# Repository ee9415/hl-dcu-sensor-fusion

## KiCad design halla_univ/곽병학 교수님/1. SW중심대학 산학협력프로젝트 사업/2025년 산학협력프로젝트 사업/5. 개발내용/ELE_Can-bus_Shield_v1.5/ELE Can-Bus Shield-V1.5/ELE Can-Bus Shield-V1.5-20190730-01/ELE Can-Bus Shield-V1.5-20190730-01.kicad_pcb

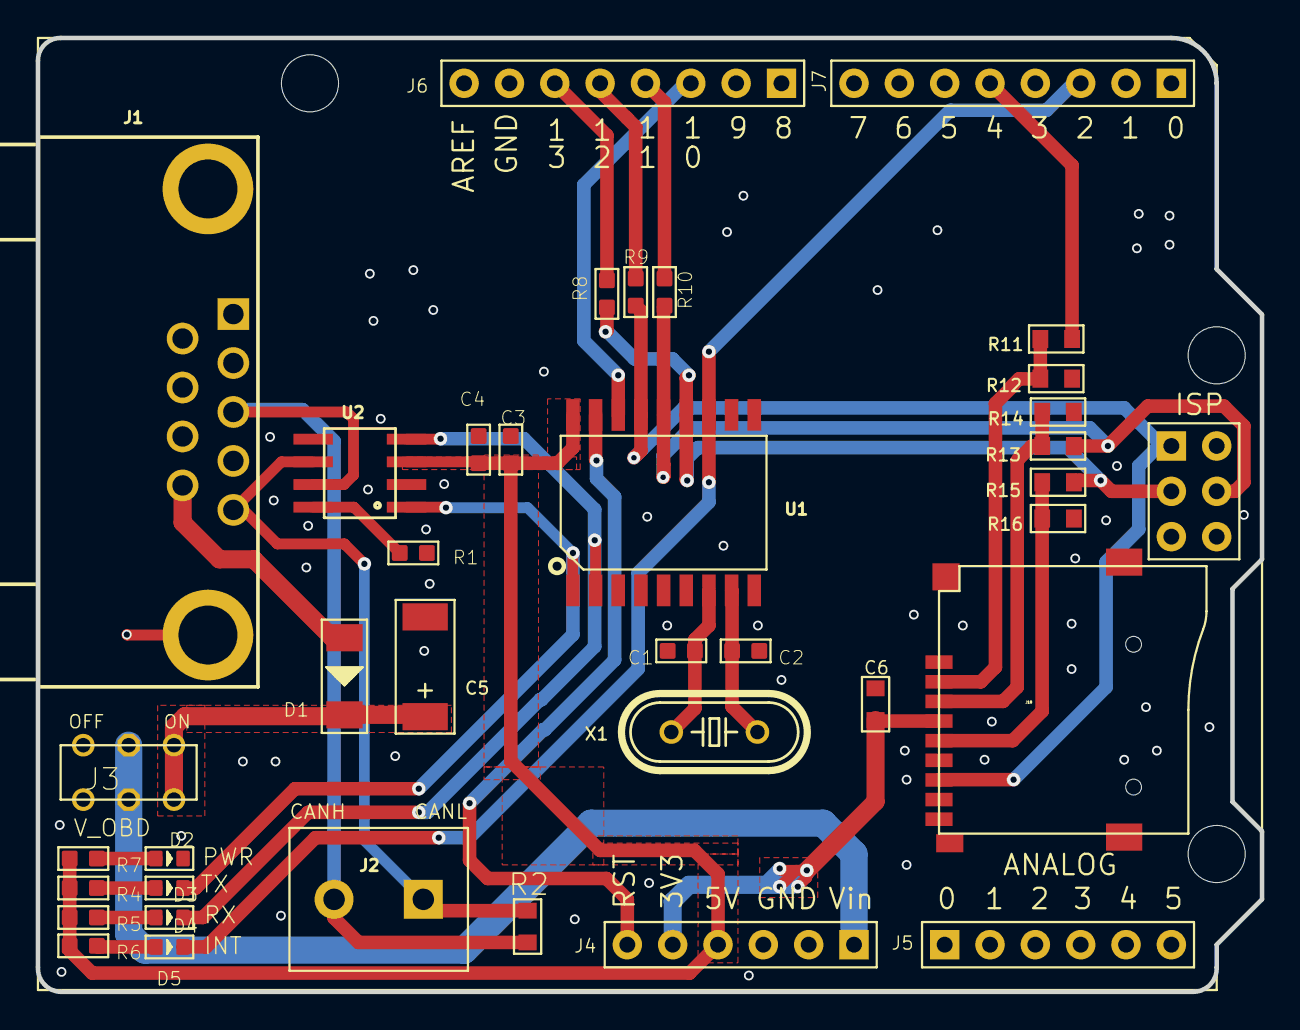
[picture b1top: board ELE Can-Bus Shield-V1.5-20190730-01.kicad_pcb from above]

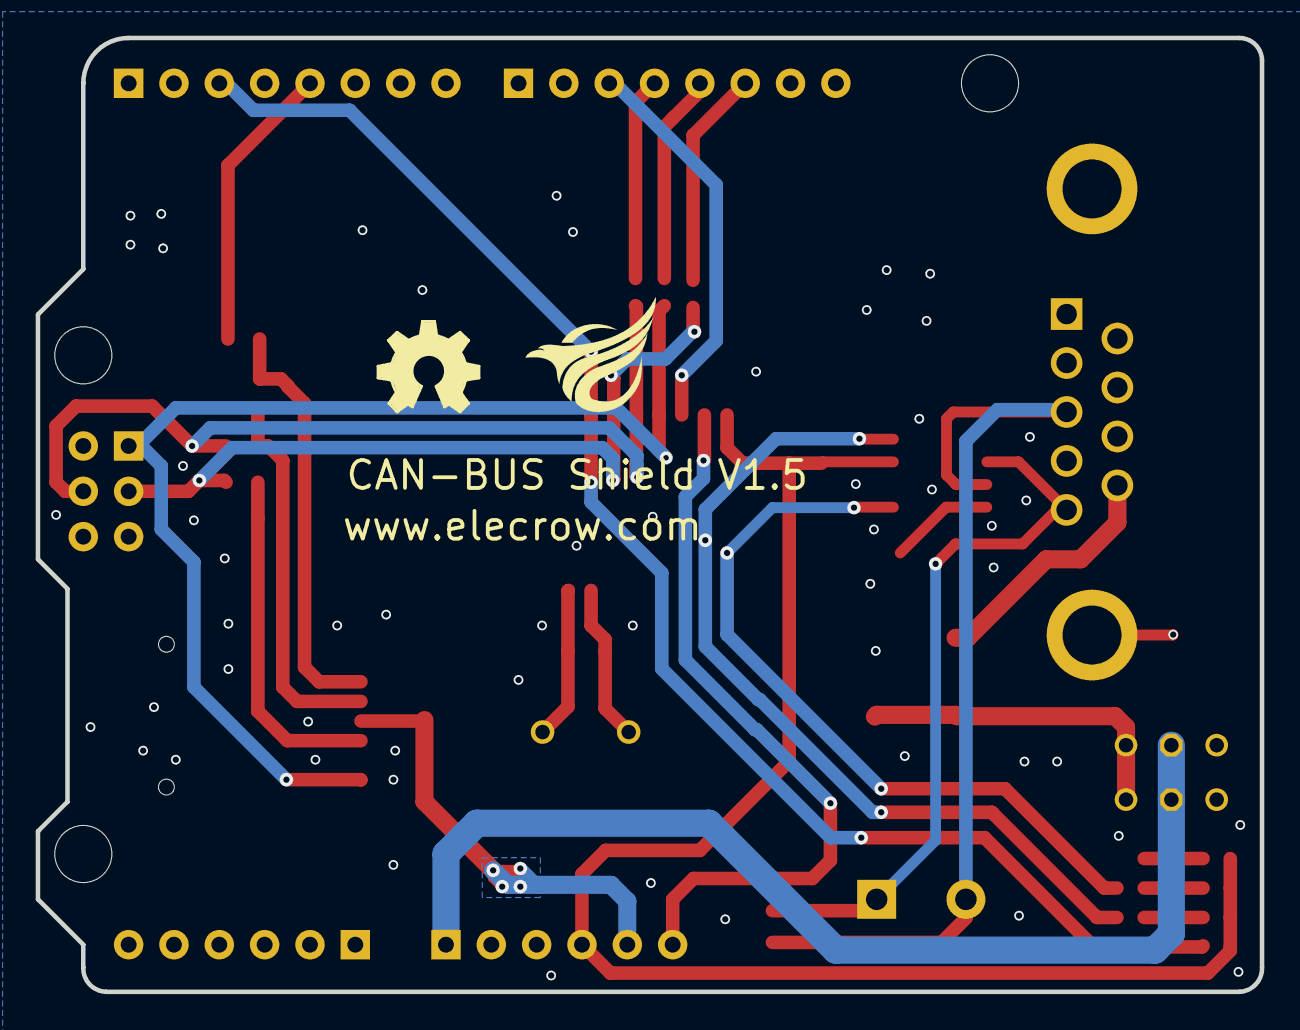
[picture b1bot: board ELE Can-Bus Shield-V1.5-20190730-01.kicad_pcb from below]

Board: 2 copper layers, 68.6 x 53.4 mm, 36 parts (2 on the bottom side), 30 nets.

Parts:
C1, C2: 22pF; 0603
C3, C4, C6: 100nF; 0603
C5: 22uF_25V; AVX-C
D1: M7; D2010
D2: GREEN; LED-0603
D3, D4, D5: RED; LED-0603
J1: DB9-MEAL
J2: 2P-5.0
J3: V_OBD; 6P-2CH-2.54-7.6X3.0
J18: 9P-SMD-W_-RING
R1: 47k; R0603
R2: NC/60R; 0603
R4, R5, R6, R7: 1k; R0603
R8, R9, R10: NC/0R; DISCRETE_R0603
R11, R13, R15: 1.8k; 0603
R12, R14, R16: 3.3k; 0603
U1: MCP2515; SOIC18
U2: MCP2551; SO08
U4: ARDUINO
U$1: ELECROW_NRW_6
U$2: OSHW_FILLX200_NOTEXT
X1: 16MHz; HC49_S

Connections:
3V3: C6.2, J18.4, U4.27
5V: C3.1, C4.1, R4.2, R5.2, R6.2, R7.2, U1.18, U2.3, U4.26
CANH: J1.3, J2.2, R2.1, U2.7
CANL: J1.5, J2.1, R2.2, U2.6
CAN_CS: U1.16, U4.11
CS: R11.1, U4.5
CS_SD: J18.2, R11.2, R12.1
GND: C1.1, C2.1, C3.2, C4.2, C5.-, C6.1, D2.-, J1.1, J1.2, J1.G1, J1.G2, J18.6, J18.G1, J18.G2, J18.G3, J18.G4, R1.2, R12.2, R14.2, R16.2, U1.9, U2.2, U4.15, U4.24, U4.25
INT: D5.-, U1.12, U4.3
MISO: J18.7, R9.2, U1.15, U4.36
MOSI: R10.2, R13.1, U1.14, U4.32
MOSI_SD: J18.3, R13.2, R14.1
unnamed: D2.+, R7.1
unnamed: D3.+, R4.1
unnamed: R8.1, U4.14
unnamed: R9.1, U4.13
unnamed: R10.1, U4.12
unnamed: D4.+, R5.1
unnamed: C1.2, U1.7, X1.2
unnamed: C2.2, U1.8, X1.1
unnamed: D5.+, R6.1
unnamed: R1.1, U2.8
RST: U1.17, U4.28
RX_CAN: D4.-, U1.2, U2.4
SCK: R8.2, R15.1, U1.13, U4.35
SCK_SD: J18.5, R15.2, R16.1
TX_CAN: D3.-, U1.1, U2.1
V+: C5.+, D1.-, J3.CH1A, J3.CH2A
VIN: J3.COM1, J3.COM2, U4.23
V_OBD: D1.+, J1.9
